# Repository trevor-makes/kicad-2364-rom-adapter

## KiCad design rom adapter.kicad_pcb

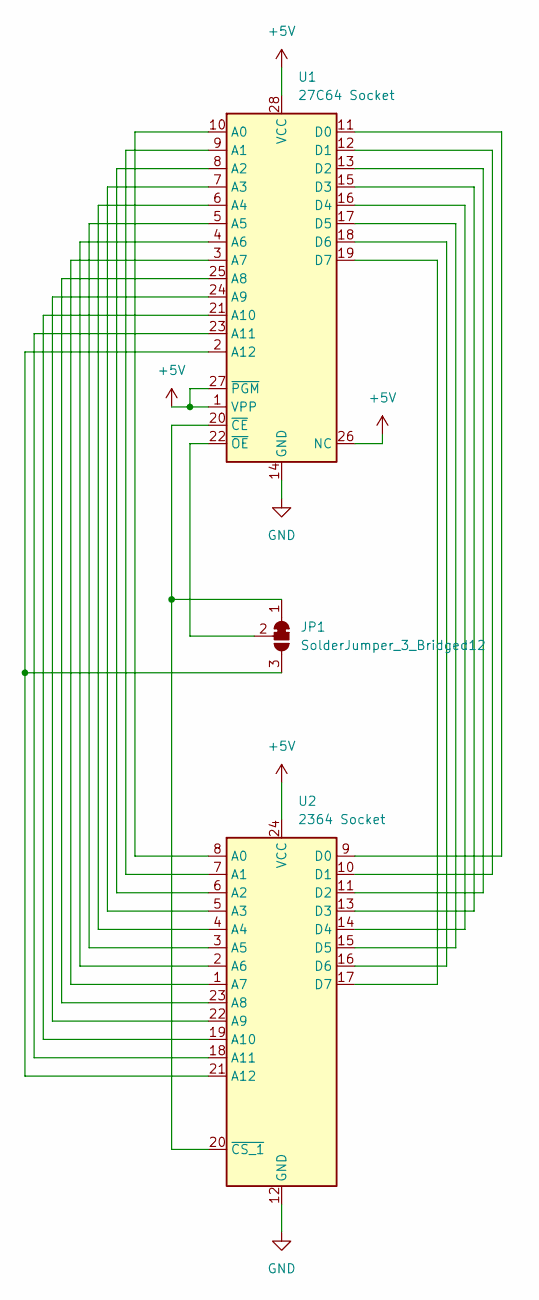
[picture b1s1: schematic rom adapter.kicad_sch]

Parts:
JP1: SolderJumper_3_Bridged12; SolderJumper-3_P1.3mm_Bridged12_Pad1.0x1.5mm
U1: 27C64 Socket; DIP-28_W15.24mm_Socket
U2: 2364 Socket; PinHeaderSocket_2x12_P2.54mm_W15.24mm

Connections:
+5V: U1.1 (VPP), U1.26 (NC), U1.27 (~PGM), U1.28 (VCC), U2.24 (VCC)
GND: U1.14 (GND), U2.12 (GND)
unnamed: JP1.1 (A), U1.20 (~CE), U2.20 (~CS_1)
unnamed: JP1.3 (B), U1.2 (A12), U2.21 (A12)
unnamed: JP1.2 (C), U1.22 (~OE)
unnamed: U1.10 (A0), U2.8 (A0)
unnamed: U1.9 (A1), U2.7 (A1)
unnamed: U1.8 (A2), U2.6 (A2)
unnamed: U1.7 (A3), U2.5 (A3)
unnamed: U1.6 (A4), U2.4 (A4)
unnamed: U1.5 (A5), U2.3 (A5)
unnamed: U1.4 (A6), U2.2 (A6)
unnamed: U1.3 (A7), U2.1 (A7)
unnamed: U1.25 (A8), U2.23 (A8)
unnamed: U1.24 (A9), U2.22 (A9)
unnamed: U1.21 (A10), U2.19 (A10)
unnamed: U1.23 (A11), U2.18 (A11)
unnamed: U1.11 (D0), U2.9 (D0)
unnamed: U1.12 (D1), U2.10 (D1)
unnamed: U1.13 (D2), U2.11 (D2)
unnamed: U1.15 (D3), U2.13 (D3)
unnamed: U1.16 (D4), U2.14 (D4)
unnamed: U1.17 (D5), U2.15 (D5)
unnamed: U1.18 (D6), U2.16 (D6)
unnamed: U1.19 (D7), U2.17 (D7)

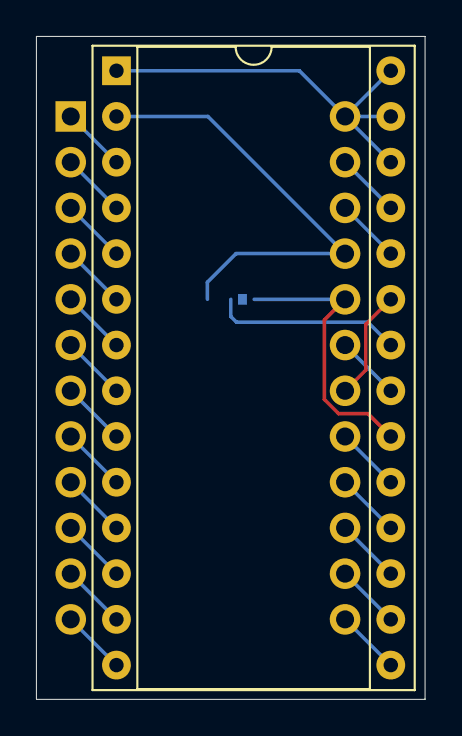
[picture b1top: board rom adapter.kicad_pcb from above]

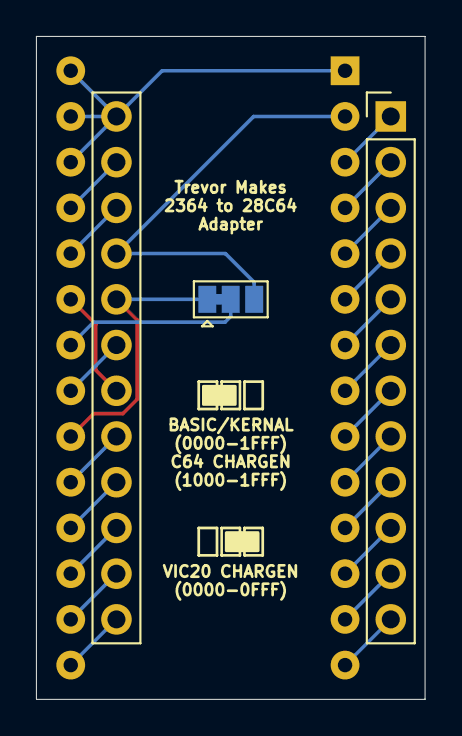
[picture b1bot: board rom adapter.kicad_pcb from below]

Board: 2 copper layers, 21.6 x 36.8 mm, 3 parts (2 on the bottom side), 25 nets.

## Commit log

2024-06-24 First revision board
